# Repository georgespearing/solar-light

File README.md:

# solar-light
Rebuild the Solar lights

1 AA Battery with a small solar panel to light a string of lights. 

Using the solar panel, this will automatically come on at night and turn off during the day. 

Know Issues / Room for Improvement

- There is no charge protection from the solar panel to battery
- R1 can be used for "tune" when the lights will turn on
- The lights will say on all night, but without a very sunny day afterward, it will die quickly the next night

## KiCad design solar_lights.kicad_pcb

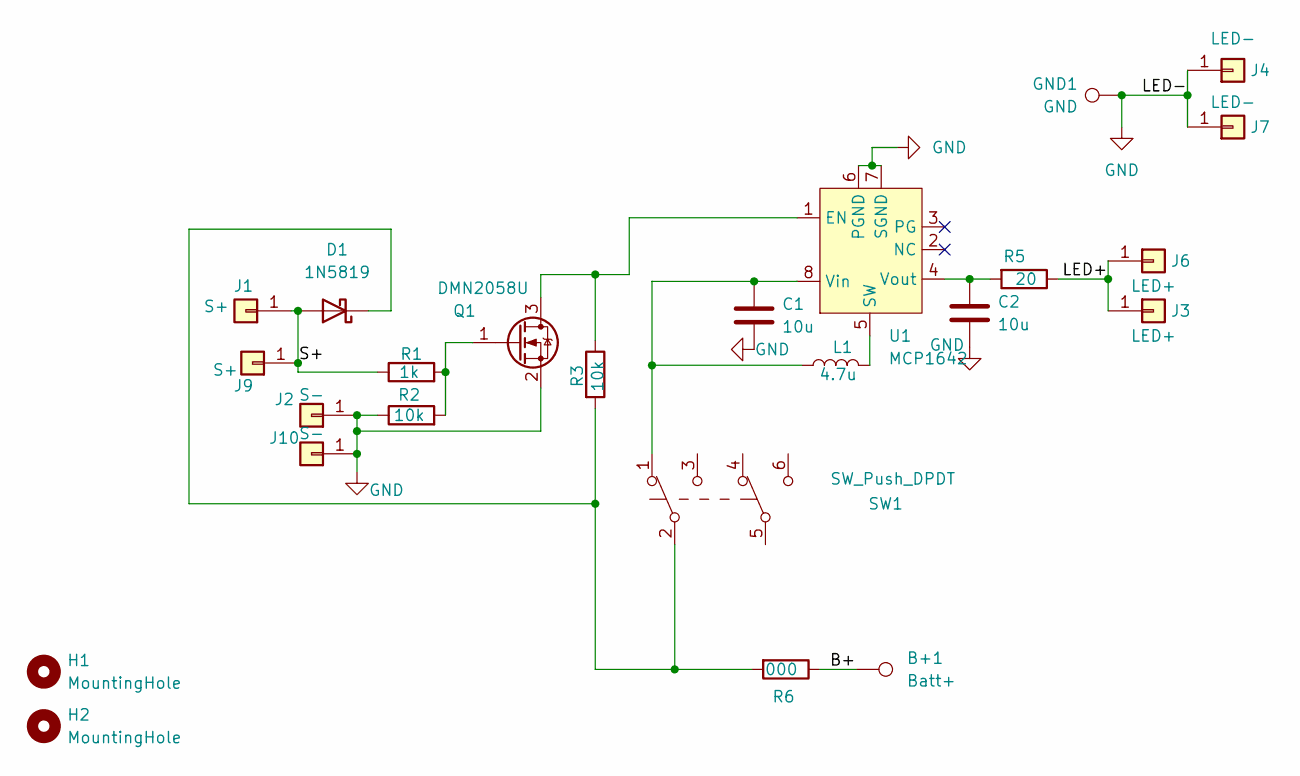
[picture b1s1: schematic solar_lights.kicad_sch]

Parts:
B+1: Batt+; TestPoint_Pad_4.0x4.0mm
C1, C2: 10u; C_0603_1608Metric_Pad1.08x0.95mm_HandSolder
D1: 1N5819; D_2512_6332Metric_Pad1.52x3.35mm_HandSolder
GND1: GND; TestPoint_Pad_4.0x4.0mm
H1, H2: MountingHole; MountingHole_2.5mm
J1, J9: S+; MountingHole_2.5mm_Pad_TopBottom
J2, J10: S-; MountingHole_2.5mm_Pad_TopBottom
J3, J6: LED+; MountingHole_2.5mm_Pad_TopBottom
J4, J7: LED-; MountingHole_2.5mm_Pad_TopBottom
L1: 4.7u; L_0603_1608Metric_Pad1.05x0.95mm_HandSolder
Q1: DMN2058U; SOT-23
R1: 1k; R_0603_1608Metric_Pad0.98x0.95mm_HandSolder
R2, R3: 10k; R_0603_1608Metric_Pad0.98x0.95mm_HandSolder
R5: 20; R_0603_1608Metric_Pad0.98x0.95mm_HandSolder
R6: 000; R_0603_1608Metric_Pad0.98x0.95mm_HandSolder
SW1: SW_Push_DPDT; SW_DPDT_6POS
U1: MCP1642; MSOP-8-1EP_3x3mm_P0.65mm_EP1.73x1.85mm_ThermalVias

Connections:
/B+: B+1.1, R6.1
/LED+: J3.1, J6.1, R5.1
/S+: D1.2 (A), J1.1, J9.1, R1.1
GND: C1.2, C2.2, GND1.1, J2.1, J4.1, J7.1, J10.1, Q1.2 (S), R2.1, U1.6 (PGND), U1.7 (SGND)
unnamed: C1.1, L1.1, SW1.1 (A), U1.8 (Vin)
unnamed: C2.1, R5.2, U1.4 (Vout)
unnamed: D1.1 (K), R3.2, R6.2, SW1.2 (B)
unnamed: L1.2, U1.5 (SW)
unnamed: Q1.1 (G), R1.2, R2.2
unnamed: Q1.3 (D), R3.1, U1.1 (EN)

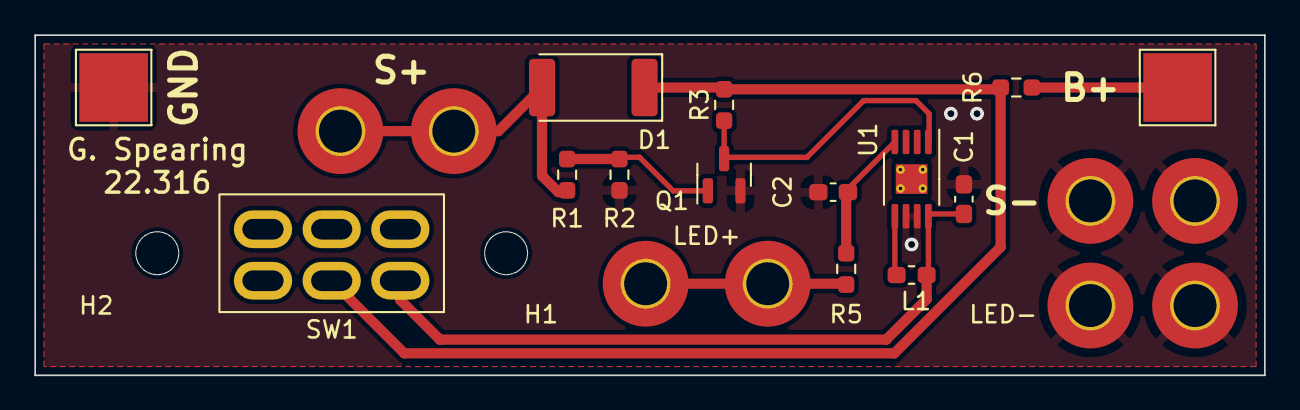
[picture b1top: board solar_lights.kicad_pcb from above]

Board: 2 copper layers, 71.6 x 19.8 mm, 24 parts (0 on the bottom side), 10 nets.

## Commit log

2022-12-04 solar lights files
